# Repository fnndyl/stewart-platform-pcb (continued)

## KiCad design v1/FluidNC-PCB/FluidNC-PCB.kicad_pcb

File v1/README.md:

## Generic 6-Axis Stepper Driver Board
### Compatible with FluidNC and ESP32-WROOM DevKit

Designed for controlling a Stewart Platform, but applicable to any application for which FluidNC is desired to drive steppers with all the bells and whistles that comes with a CNC firmware package. 

Designed using KiCad 9.0. Ordered through JLCPCB. All components are through-hole and expected to be hand soldered. Uses cheap Wroom Devkit, molex connectors for motors and limit switches, and DRV8825 stepstick drivers. *It may be possible to use fancier drivers - not tested, PCB may require modification.*

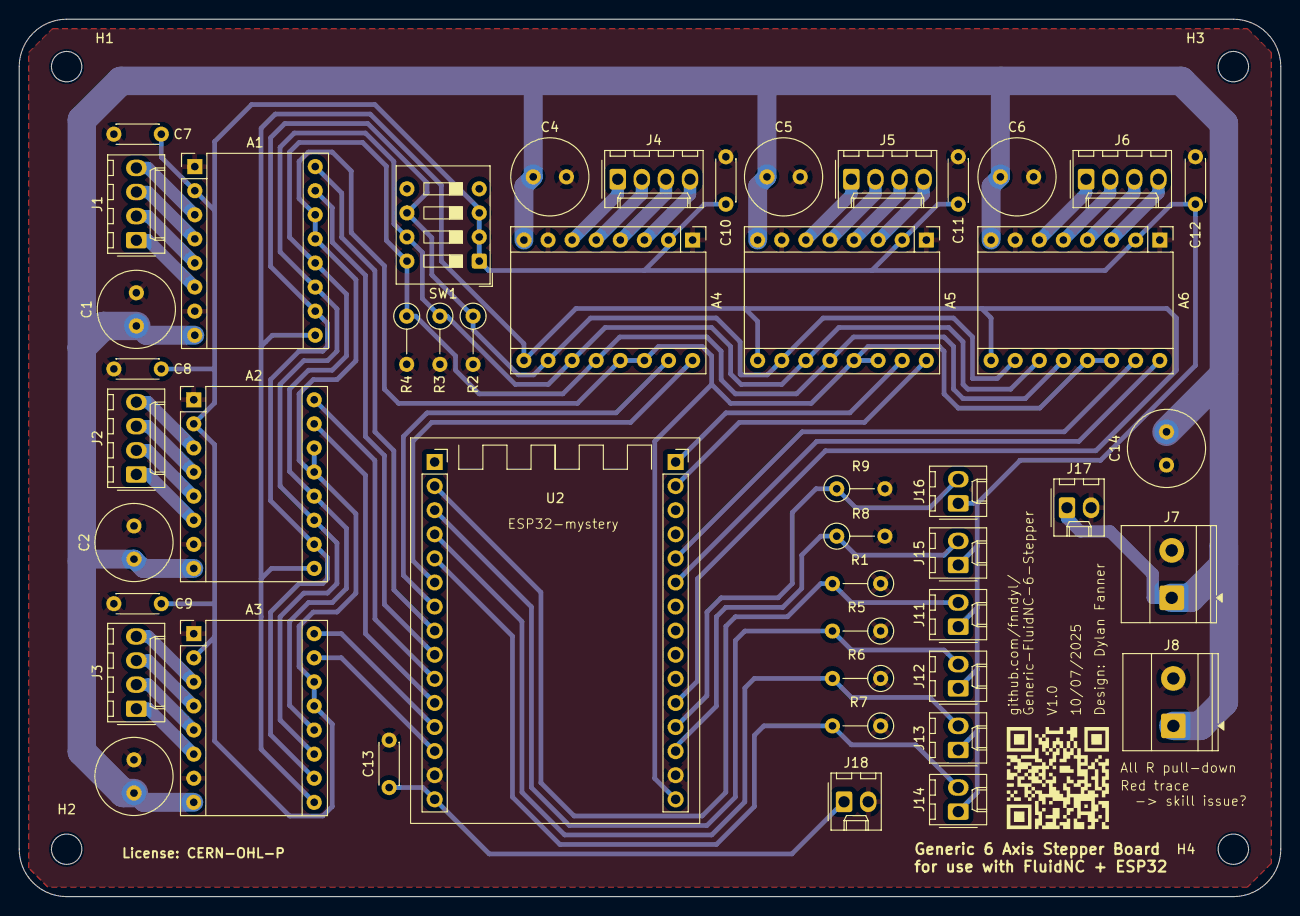
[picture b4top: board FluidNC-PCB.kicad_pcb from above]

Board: 2 copper layers, 133.0 x 92.5 mm, 51 parts (0 on the bottom side), 50 nets.

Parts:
A1, A2, A3, A4, A5, A6: Pololu_Breakout_A4988; Pololu_Breakout-16_15.2x20.3mm
C1, C2, C3, C4, C5, C6, C14: 33uF; C_Radial_D8.0mm_H11.5mm_P3.50mm
C7, C8, C9, C10, C11, C12, C13: 100nF; C_Disc_D4.3mm_W1.9mm_P5.00mm
H1, H2, H3, H4: MountingHole; MountingHole_3.2mm_M3
J1, J2, J3, J4, J5, J6: Conn_01x04_Pin; Molex_KK-254_AE-6410-04A_1x04_P2.54mm_Vertical
J7: 12V Power Input; TerminalBlock_Phoenix_MKDS-1,5-2_1x02_P5.00mm_Horizontal
J8: Fan Screw Terminal; TerminalBlock_Phoenix_MKDS-1,5-2_1x02_P5.00mm_Horizontal
J11, J12, J13, J14, J15, J16, J17, J18: Molex_01x02_Socket; Molex_KK-254_AE-6410-02A_1x02_P2.54mm_Vertical
R1, R2, R3, R4, R5, R6, R7, R8, R9: R22k; R_Axial_DIN0207_L6.3mm_D2.5mm_P5.08mm_Vertical
SW1: SW_DIP_x04; SW_DIP_SPSTx04_Slide_9.78x12.34mm_W7.62mm_P2.54mm
U2: esp32-mystery-footprint

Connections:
+3.3V: A1.2 (VDD), A1.13 (~RESET), A1.14 (~SLEEP), A2.2 (VDD), A2.13 (~RESET), A2.14 (~SLEEP), A3.2 (VDD), A3.13 (~RESET), A3.14 (~SLEEP), A4.2 (VDD), A4.13 (~RESET), A4.14 (~SLEEP), A5.2 (VDD), A5.13 (~RESET), A5.14 (~SLEEP), A6.2 (VDD), A6.13 (~RESET), A6.14 (~SLEEP), C7.1, C8.1, C9.1, C10.1, C11.1, C12.1, J11.1, J12.1, J13.1, J14.1, J15.1, J16.1, SW1.1, SW1.2, SW1.3, U2.16 (3V3)
+5V: C13.1, J18.1, U2.15 (VIN)
+12V: A1.8 (VMOT), A2.8 (VMOT), A3.8 (VMOT), A4.8 (VMOT), A5.8 (VMOT), A6.8 (VMOT), C1.1, C2.1, C3.1, C4.1, C5.1, C6.1, C14.1, J7.1, J8.1, J17.1
ENABLE_N: A1.9 (~ENABLE), A2.9 (~ENABLE), A3.9 (~ENABLE), A4.9 (~ENABLE), A5.9 (~ENABLE), A6.9 (~ENABLE), U2.20 (D4)
GND: A1.1 (GND), A1.7 (GND), A2.1 (GND), A2.7 (GND), A3.1 (GND), A3.7 (GND), A4.1 (GND), A4.7 (GND), A5.1 (GND), A5.7 (GND), A6.1 (GND), A6.7 (GND), C1.2, C2.2, C3.2, C4.2, C5.2, C6.2, C7.2, C8.2, C9.2, C10.2, C11.2, C12.2, C13.2, C14.2, J7.2, J8.2, J17.2, J18.2, R1.1, R2.2, R3.2, R4.2, R5.1, R6.1, R7.1, R8.2, R9.2, U2.14 (GND), U2.17 (GND)
M0_DIR: A1.16 (DIR), U2.8 (D25)
M0_STP: A1.15 (STEP), U2.9 (D26)
M1_DIR: A2.16 (DIR), U2.10 (D27)
M1_STP: A2.15 (STEP), U2.11 (D14)
M2_DIR: A3.16 (DIR), U2.12 (D12)
M2_STP: A3.15 (STEP), U2.13 (D13)
M3_DIR: A4.16 (DIR), U2.6 (D32)
M3_STP: A4.15 (STEP), U2.7 (D33)
M4_DIR: A5.16 (DIR), U2.29 (D22)
M4_STP: A5.15 (STEP), U2.30 (D23)
M5_DIR: A6.16 (DIR), U2.25 (D19)
M5_STP: A6.15 (STEP), U2.26 (D21)
unnamed: A1.4 (1A), J1.3
unnamed: A1.3 (1B), J1.4
unnamed: A1.5 (2A), J1.2
unnamed: A1.6 (2B), J1.1
unnamed: A1.10 (MS1), A2.10 (MS1), A3.10 (MS1), A4.10 (MS1), A5.10 (MS1), A6.10 (MS1), R2.1, SW1.6
unnamed: A1.11 (MS2), A2.11 (MS2), A3.11 (MS2), A4.11 (MS2), A5.11 (MS2), A6.11 (MS2), R3.1, SW1.7
unnamed: A1.12 (MS3), A2.12 (MS3), A3.12 (MS3), A4.12 (MS3), A5.12 (MS3), A6.12 (MS3), R4.1, SW1.8
unnamed: A2.4 (1A), J2.3
unnamed: A2.3 (1B), J2.4
unnamed: A2.5 (2A), J2.2
unnamed: A2.6 (2B), J2.1
unnamed: A3.4 (1A), J3.3
unnamed: A3.3 (1B), J3.4
unnamed: A3.5 (2A), J3.2
unnamed: A3.6 (2B), J3.1
unnamed: A4.4 (1A), J4.3
unnamed: A4.3 (1B), J4.4
unnamed: A4.5 (2A), J4.2
unnamed: A4.6 (2B), J4.1
unnamed: A5.4 (1A), J5.3
unnamed: A5.3 (1B), J5.4
unnamed: A5.5 (2A), J5.2
unnamed: A5.6 (2B), J5.1
unnamed: A6.4 (1A), J6.3
unnamed: A6.3 (1B), J6.4
unnamed: A6.5 (2A), J6.2
unnamed: A6.6 (2B), J6.1
unnamed: J11.2, R1.2, U2.2 (VP/D36)
unnamed: J12.2, R5.2, U2.3 (VN/D39)
unnamed: J13.2, R6.2, U2.4 (D34)
unnamed: J14.2, R7.2, U2.5 (D35)
unnamed: J15.2, R8.1, U2.18 (D15)
unnamed: J16.2, R9.1, U2.19 (D2)

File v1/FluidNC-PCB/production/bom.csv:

Designator,Footprint,Quantity,Value,LCSC Part #
"A1, A2, A3, A4, A5, A6",Pololu_Breakout-16_15.2x20.3mm,6,Pololu_Breakout_A4988,
"C1, C14, C2, C3, C4, C5, C6",C_Radial_D8.0mm_H11.5mm_P3.50mm,7,33uF,
"C10, C11, C12, C13, C7, C8, C9",C_Disc_D4.3mm_W1.9mm_P5.00mm,7,100nF,
"J1, J2, J3, J4, J5, J6",Molex_KK-254_AE-6410-04A_1x04_P2.54mm_Vertical,6,Conn_01x04_Pin,
"J11, J12, J13, J14, J15, J16, J17, J18",Molex_KK-254_AE-6410-02A_1x02_P2.54mm_Vertical,8,Molex_01x02_Socket,
J7,"TerminalBlock_Phoenix_MKDS-1,5-2_1x02_P5.00mm_Horizontal",1,12V Power Input,
J8,"TerminalBlock_Phoenix_MKDS-1,5-2_1x02_P5.00mm_Horizontal",1,Fan Screw Terminal,
"R1, R2, R3, R4, R5, R6, R7, R8, R9",R_Axial_DIN0207_L6.3mm_D2.5mm_P5.08mm_Vertical,9,R22k,
SW1,SW_DIP_SPSTx04_Slide_9.78x12.34mm_W7.62mm_P2.54mm,1,SW_DIP_x04,
U2,esp32-mystery-footprint,1,~,

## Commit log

2025-08-27 Working on config
2025-08-27 Config v1 done
2026-04-03 Start of new pcb
2026-04-04 Adding stepper drivers if needed/wanted. A4988 or TMC2209/TMC2208 compatible.
2026-04-04 PCB 2 x Stepper Drivers
2026-04-08 Before rotations
2026-04-08 Arranging in circle
2026-04-08 Found working outline
2026-05-11 Little board I think
2026-05-14 SolderJig added
